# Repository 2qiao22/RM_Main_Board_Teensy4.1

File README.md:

# RM_NAGOYA_Main_Control_Board

## Overview
A main control board for robot control in the RoboMaster competition.

## Specifications
- **MCU**: Teensy 4.1  
- **IMU**: BNO055  
- **CAN**: 3 channels  
 
- **Design Tool**: KiCad 9.0

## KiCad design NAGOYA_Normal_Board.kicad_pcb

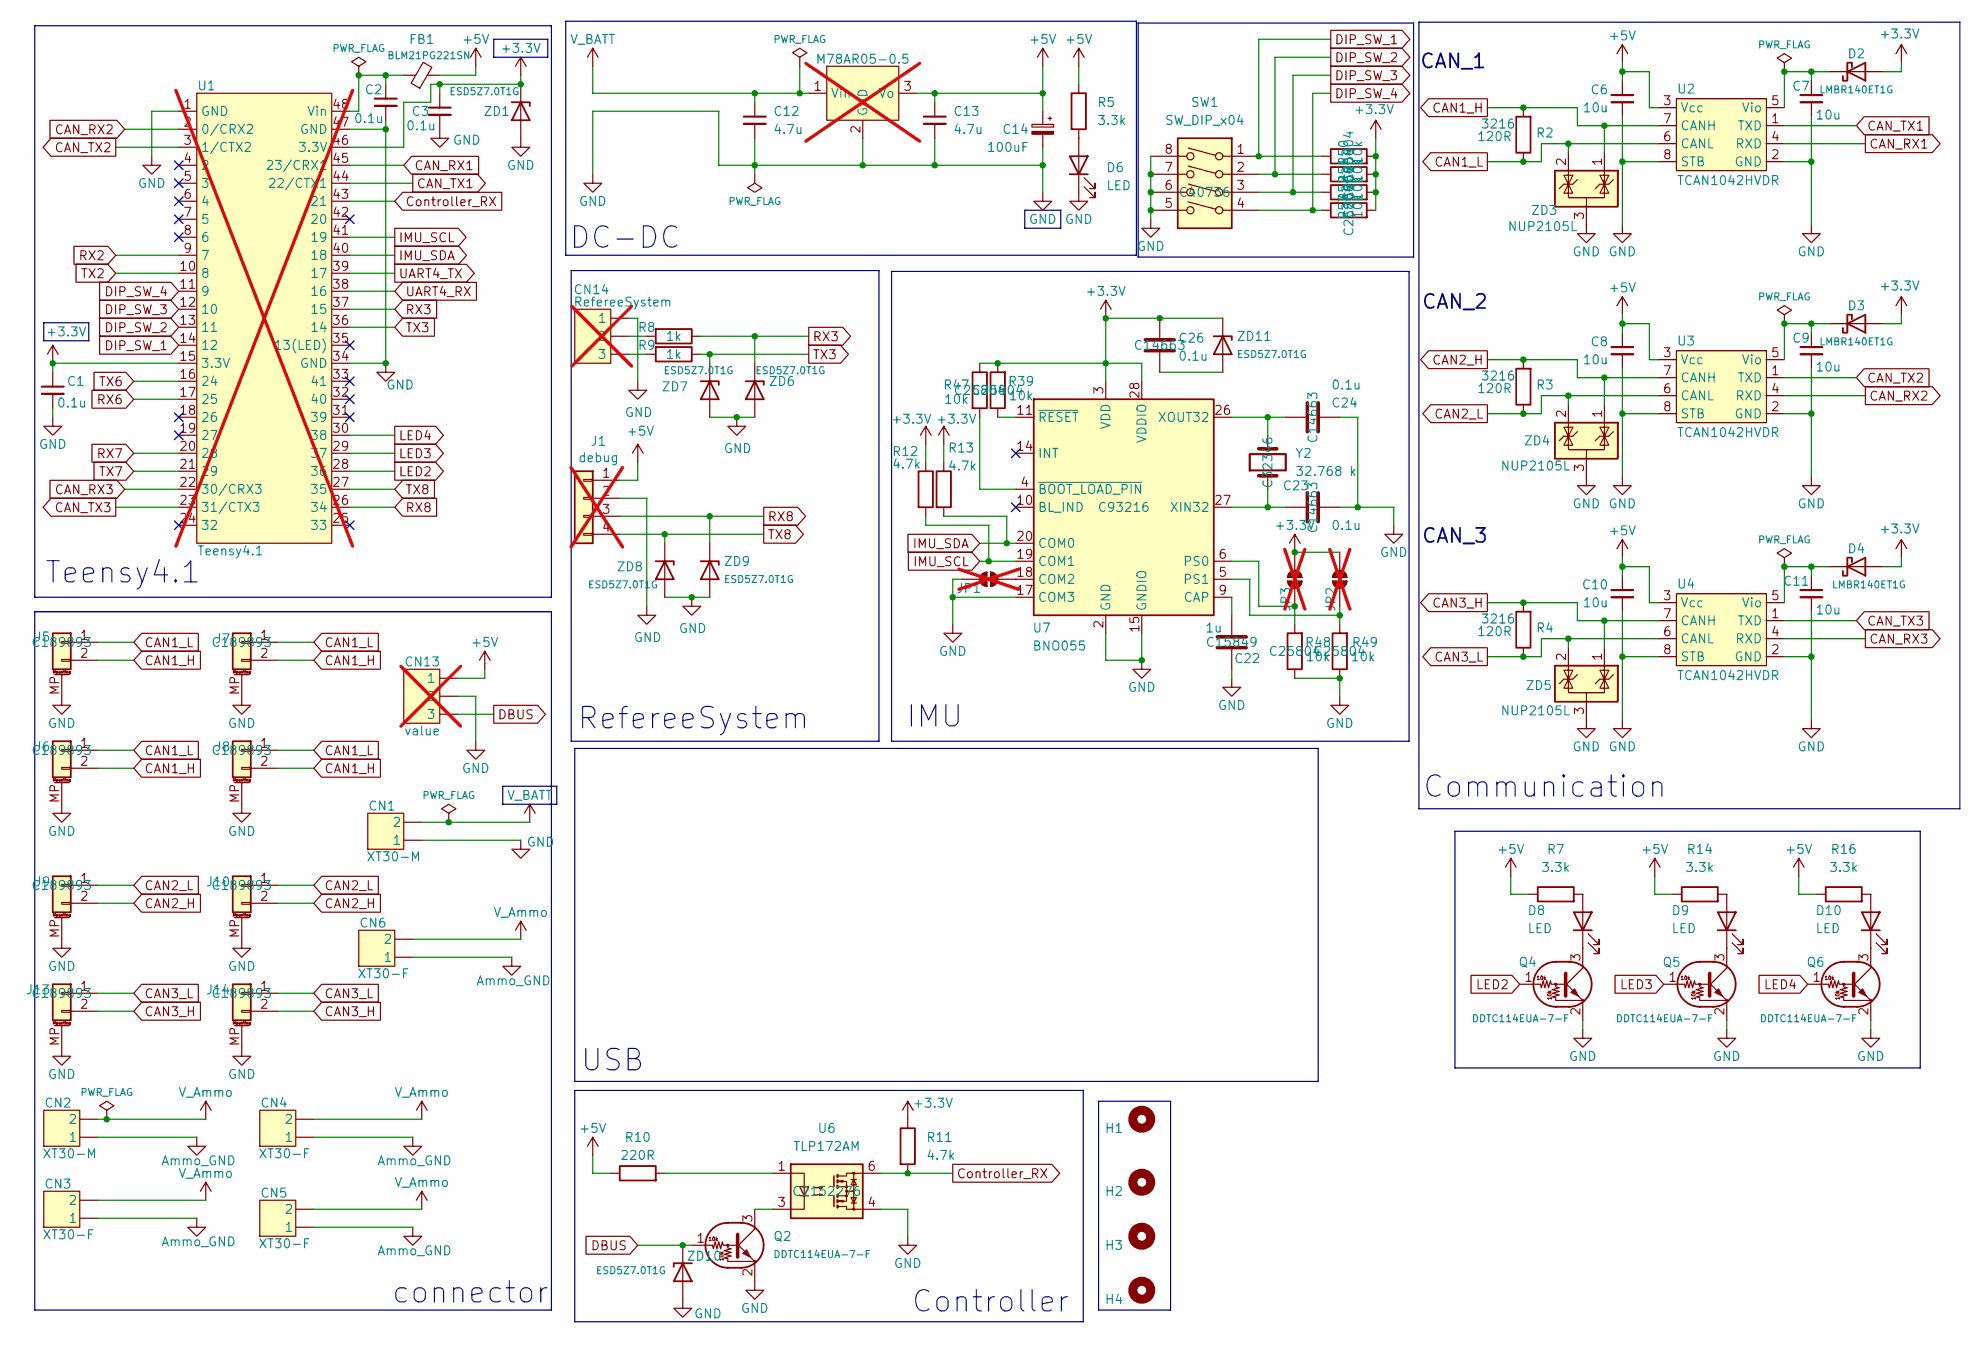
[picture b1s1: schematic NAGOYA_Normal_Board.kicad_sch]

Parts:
C1, C2, C3, C23, C24, C26: 0.1u; C_0603_1608Metric; LCSC C14663
C6, C7, C8, C9, C10, C11: 10u; C_1206_3216Metric; LCSC C13585
C12, C13: 4.7u; C_1206_3216Metric; LCSC C29823
C14: 100uF; CP_Elec_6.3x7.7; LCSC C3338
C22: 1u; C_0603_1608Metric; LCSC C15849
CN1, CN2: XT30-M; AMASS_XT30U-M_1x02_P5.0mm_Vertical; LCSC C428721
CN3, CN4, CN5, CN6: XT30-F; AMASS_XT30U-F_1x02_P5.0mm_Vertical; LCSC C108769
CN13: value; PinHeader_1x03_P2.54mm_Vertical; not fitted
CN14: RefereeSystem; JST_XH_B3B-XH-AM_1x03_P2.50mm_Vertical; not fitted
D2, D3, D4: LMBR140ET1G; D_TUMD2; LCSC C172430
D6, D8, D9, D10: LED; LED_0603_1608Metric; LCSC C510027
FB1: BLM21PG221SN; R_0805_2012Metric; LCSC C85840
H1, H2, H3, H4: MountingHole; MountingHole_3.2mm_M3_ISO14580
J1: debug; JST_XH_B4B-XH-A_1x04_P2.50mm_Vertical; LCSC C722867; not fitted
J5, J6, J7, J8, J9, J10, J13, J14: CAN3; JST_GH_SM02B-GHS-TB_1x02-1MP_P1.25mm_Horizontal; LCSC C189893
JP1, JP2, JP3: SolderJumper_2_Open; SolderJumper-2_P1.3mm_Open_TrianglePad1.0x1.5mm; not fitted
M78AR05-0.5: SIP3_LMS78-12_GAP; not fitted
Q2, Q4, Q5, Q6: DDTC114EUA-7-F; SOT-323_SC-70; LCSC C177021
R2, R3, R4: 120R; R_1206_3216Metric; LCSC C17909
R5, R7, R14, R16: 3.3k; R_0603_1608Metric; LCSC C4109
R8, R9: 1k; R_0603_1608Metric; LCSC C21190
R10: 220R; R_0603_1608Metric; LCSC C22962
R11, R12, R13: 4.7k; R_0805_2012Metric; LCSC C17673
R39, R47, R48, R49, R50, R51, R52, R53: 10k; R_0603_1608Metric; LCSC C25804
SW1: SW_DIP_x04; SW_DIP_SPSTx04_Slide_Copal_CHS-04B_W7.62mm_P1.27mm; LCSC C40736
U1: Teensy4.1; DIP-48_W15.24mm_Socket_LongPads; not fitted
U2, U3, U4: TCAN1042HVDR; SOIC-8_3.9x4.9mm_P1.27mm; LCSC C485807
U6: TLP172AM; MFSOP6-4_4.4x3.6mm_P1.27mm; LCSC C2152276
U7: BNO055; LGA-28_5.2x3.8mm_P0.5mm; LCSC C93216
Y2: 32.768 k; Crystal_SMD_3215-2Pin_3.2x1.5mm; LCSC C32346
ZD1, ZD6, ZD7, ZD8, ZD9, ZD10, ZD11: ESD5Z7.0T1G; D_SOD-523; LCSC C133093
ZD3, ZD4, ZD5: NUP2105L; SOT-23; LCSC C14486

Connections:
+3.3V: C1.1, C3.1, C26.1, D2.2 (A), D3.2 (A), D4.2 (A), JP2.1 (A), JP3.1 (A), R11.1, R12.1, R13.1, R39.2, R47.1, R50.2, R51.2, R52.2, R53.2, U1.15 (3.3V), U1.46 (3.3V), U7.3 (VDD), U7.28 (VDDIO), ZD1.1 (K), ZD11.1 (K)
+5V: C6.1, C8.1, C10.1, C13.1, C14.1, CN13.1, FB1.2, J1.1, M78AR05-0.5.3 (Vo), R5.1, R7.1, R10.1, R14.1, R16.1, U2.3 (Vcc), U3.3 (Vcc), U4.3 (Vcc)
Ammo_GND: CN2.1, CN3.1, CN4.1, CN5.1, CN6.1
CAN1_H: J5.2, J6.2, J7.2, J8.2, R2.2, U2.7 (CANH), ZD3.1 (K)
CAN1_L: J5.1, J6.1, J7.1, J8.1, R2.1, U2.6 (CANL), ZD3.2 (K)
CAN2_H: J9.2, J10.2, R3.2, U3.7 (CANH), ZD4.1 (K)
CAN2_L: J9.1, J10.1, R3.1, U3.6 (CANL), ZD4.2 (K)
CAN3_H: J13.2, J14.2, R4.2, U4.7 (CANH), ZD5.1 (K)
CAN3_L: J13.1, J14.1, R4.1, U4.6 (CANL), ZD5.2 (K)
CAN_RX1: U1.45 (23/CRX1), U2.4 (RXD)
CAN_RX2: U1.2 (0/CRX2), U3.4 (RXD)
CAN_RX3: U1.22 (30/CRX3), U4.4 (RXD)
CAN_TX1: U1.44 (22/CTX1), U2.1 (TXD)
CAN_TX2: U1.3 (1/CTX2), U3.1 (TXD)
CAN_TX3: U1.23 (31/CTX3), U4.1 (TXD)
Controller_RX: R11.2, U1.43 (21), U6.6
DBUS: CN13.3, Q2.1 (B), ZD10.1 (K)
DIP_SW_1: R50.1, SW1.1, U1.14 (12)
DIP_SW_2: R51.1, SW1.2, U1.13 (11)
DIP_SW_3: R52.1, SW1.3, U1.12 (10)
DIP_SW_4: R53.1, SW1.4, U1.11 (9)
GND: C1.2, C2.2, C3.2, C6.2, C7.2, C8.2, C9.2, C10.2, C11.2, C12.2, C13.2, C14.2, C22.2, C23.1, C24.1, CN1.1, CN13.2, CN14.1, D6.1 (K), J1.2, J5.MP (MountPin), J6.MP (MountPin), J7.MP (MountPin), J8.MP (MountPin), J9.MP (MountPin), J10.MP (MountPin), J13.MP (MountPin), J14.MP (MountPin), JP1.2 (B), M78AR05-0.5.2 (GND), Q2.2 (E), Q4.2 (E), Q5.2 (E), Q6.2 (E), R48.1, R49.1, SW1.5, SW1.6, SW1.7, SW1.8, U1.1 (GND), U1.34 (GND), U1.47 (GND), U2.2 (GND), U2.8 (STB), U3.2 (GND), U3.8 (STB), U4.2 (GND), U4.8 (STB), U6.4, U7.2 (GND), U7.15 (GNDIO), U7.16 (GNDIO), U7.17 (COM3), U7.25 (GNDIO), ZD1.2 (A), ZD3.3 (A), ZD4.3 (A), ZD5.3 (A), ZD6.2 (A), ZD7.2 (A), ZD8.2 (A), ZD9.2 (A), ZD10.2 (A)
IMU_SCL: R12.2, U1.41 (19), U7.19 (COM1)
IMU_SDA: R13.2, U1.40 (18), U7.20 (COM0)
LED2: Q4.1 (B), U1.28 (36)
LED3: Q5.1 (B), U1.29 (37)
LED4: Q6.1 (B), U1.30 (38)
unnamed: CN14.2, R8.2
unnamed: CN14.3, R9.2
unnamed: C7.1, D2.1 (K), U2.5 (Vio)
unnamed: C9.1, D3.1 (K), U3.5 (Vio)
unnamed: C11.1, D4.1 (K), U4.5 (Vio)
unnamed: D6.2 (A), R5.2
unnamed: D8.2 (A), R7.2
unnamed: D8.1 (K), Q4.3 (C)
unnamed: D9.2 (A), R14.2
unnamed: D9.1 (K), Q5.3 (C)
unnamed: D10.2 (A), R16.2
unnamed: D10.1 (K), Q6.3 (C)
unnamed: JP1.1 (A), U7.18 (COM2)
unnamed: JP2.2 (B), R49.2, U7.5 (PS1)
unnamed: JP3.2 (B), R48.2, U7.6 (PS0)
unnamed: Q2.3 (C), U6.3
unnamed: R10.2, U6.1
unnamed: C2.1, FB1.1, U1.48 (Vin)
unnamed: C22.1, U7.9 (CAP)
unnamed: C23.2, U7.27 (XIN32), Y2.1
unnamed: C24.2, U7.26 (XOUT32), Y2.2
unnamed: R47.2, U7.4 (~BOOT_LOAD_PIN)
unnamed: R39.1, U7.11 (~RESET)
unnamed: C26.2, ZD11.2 (A)
RX2: U1.9 (7)
RX3: R8.1, U1.37 (15), ZD6.1 (K)
RX6: U1.17 (25)
RX7: U1.20 (28)
RX8: J1.3, U1.26 (34), ZD9.1 (K)
TX2: U1.10 (8)
TX3: R9.1, U1.36 (14), ZD7.1 (K)
TX6: U1.16 (24)
TX7: U1.21 (29)
TX8: J1.4, U1.27 (35), ZD8.1 (K)
UART4_RX: U1.38 (16)
UART4_TX: U1.39 (17)
V_Ammo: CN2.2, CN3.2, CN4.2, CN5.2, CN6.2
V_BATT: C12.1, CN1.2, M78AR05-0.5.1 (Vin)

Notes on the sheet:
Controller
connector
IMU
CAN_1
Teensy4.1
DC-DC
CAN_3
USB
CAN_2
RefereeSystem
Communication

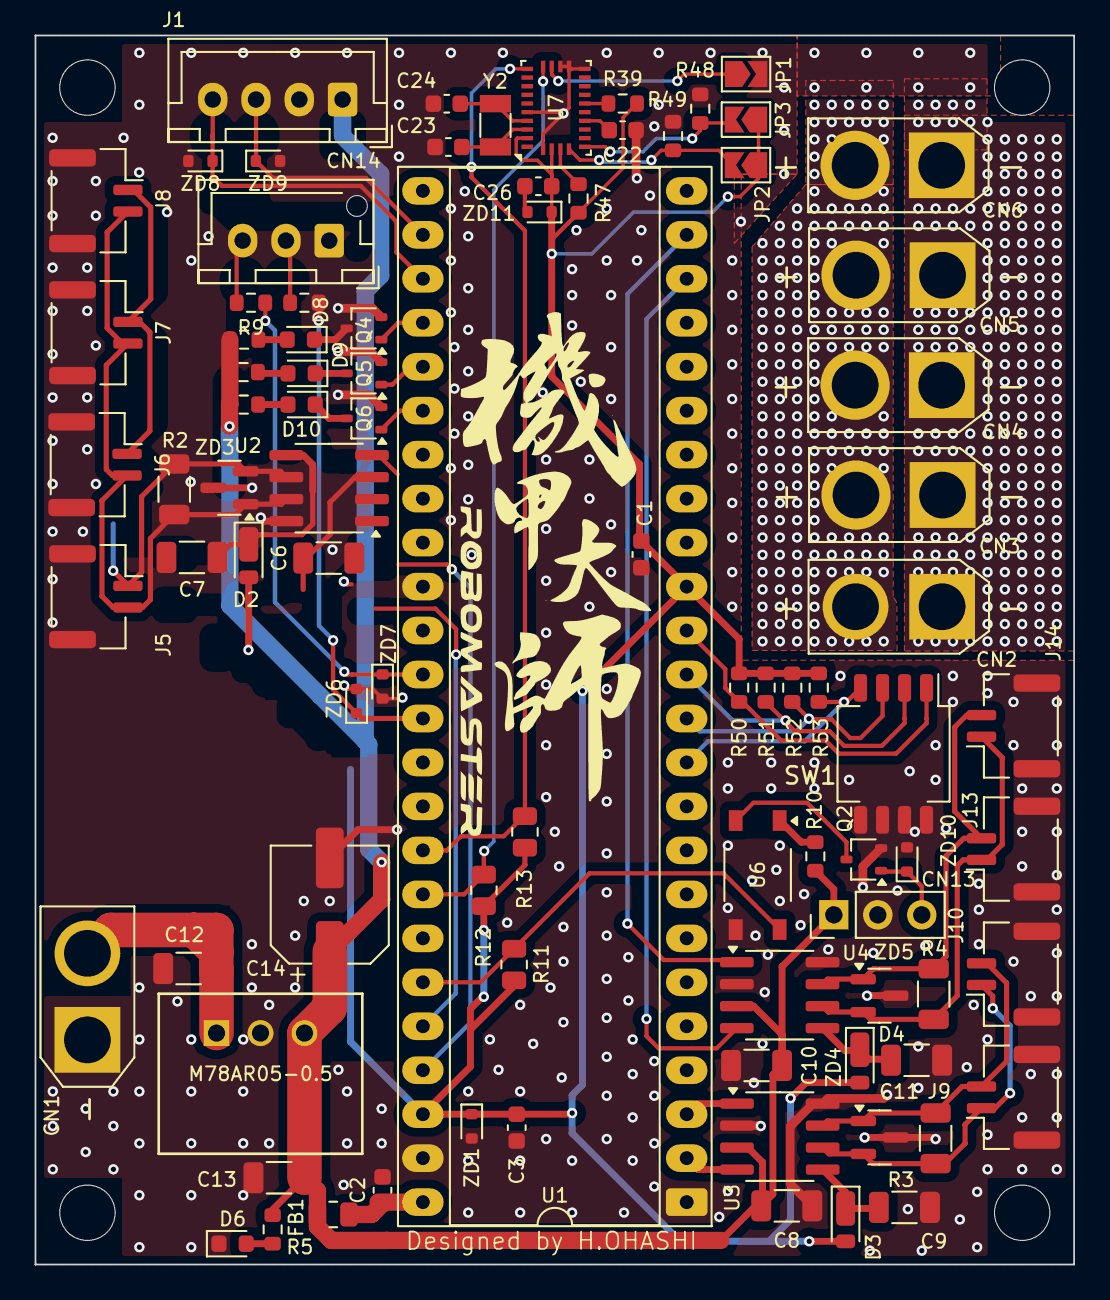
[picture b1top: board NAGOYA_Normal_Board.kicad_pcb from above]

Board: 2 copper layers, 60.0 x 71.0 mm, 92 parts (0 on the bottom side), 57 nets.

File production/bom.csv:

Designator,Footprint,Quantity,Value,LCSC Part #
"C1, C2, C23, C24, C26, C3",0603,6,0.1u,C14663
"C10, C11, C6, C7, C8, C9",1206,6,10u,C13585
"C12, C13",1206,2,4.7u,C29823
C14,CP_Elec_6.3x7.7,1,100uF,C3338
C22,0603,1,1u, C15849
"CN1, CN2",AMASS_XT30U-M_1x02_P5.0mm_Vertical,2,XT30-M,C428721
"CN3, CN4, CN5, CN6",AMASS_XT30U-F_1x02_P5.0mm_Vertical,4,XT30-F,C108769
"D10, D6, D8, D9",0603,4,LED, C510027
"D2, D3, D4",D_TUMD2,3,LMBR140ET1G,C172430
FB1,0805,1,BLM21PG221SN,C85840
"J10, J13, J14, J5, J6, J7, J8, J9",JST_GH_SM02B-GHS-TB_1x02-1MP_P1.25mm_Horizontal,8,CAN3, C189893
"Q2, Q4, Q5, Q6",SOT-323_SC-70,4,DDTC114EUA-7-F,C177021
R10,0603,1,220R,C22962
"R11, R12, R13",0805,3,4.7k,C17673
"R14, R16, R5, R7",0603,4,3.3k,C4109
"R2, R3, R4",1206,3,120R,C17909
"R39, R47, R48, R49, R50, R51, R52, R53",0603,8,10k, C25804
"R8, R9",0603,2,1k,C21190
SW1,SW_DIP_SPSTx04_Slide_Copal_CHS-04B_W7.62mm_P1.27mm,1,SW_DIP_x04,C40736 
"U2, U3, U4",SOIC-8_3.9x4.9mm_P1.27mm,3,TCAN1042HVDR,C485807
U6,MFSOP6-4_4.4x3.6mm_P1.27mm,1,TLP172AM,C2152276
U7,LGA-28_5.2x3.8mm_P0.5mm,1,BNO055,C93216
Y2,Crystal_SMD_3215-2Pin_3.2x1.5mm,1,32.768 k,C32346
"ZD1, ZD10, ZD11, ZD6, ZD7, ZD8, ZD9",D_SOD-523,7,ESD5Z7.0T1G,C133093
"ZD3, ZD4, ZD5",SOT-23,3,NUP2105L,C14486

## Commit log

2025-03-18 RS485を追加
2025-03-18 DCDCを変更
2025-03-18 USBシリアル変換を追加
2025-03-18 USB シリアルを追加
2025-04-02 PCBwo
2025-04-02 PCBを作成。また、回路図の修正（DCDC）
2025-04-03 recommit
2025-04-04 USBシリアルを絶縁＞パターン変更
2025-04-06 USBシリアルを絶縁
2025-04-13 発注用データ
2025-04-13 発注用parameterを変更
2025-04-14 シルクを修正
2025-04-14 回路図PDFを最新版に変更
2025-04-14 3Dモデルを割当
2025-04-17 USBを削除パターンを変更
